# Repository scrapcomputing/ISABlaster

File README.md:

# ISA Blaster
A PCB for a software-defined ISA card powered by a Raspberry Pi Pico micro-controller.
All the logic for interfacing to the ISA bus is done in software.

# Projects based on the ISA Blaster

## DirtyRat USB Mouse Adapter
We can use the ISA Blaster as a USB mouse adapter card.
This allows you to use a USB mouse on your vintage DOS PC without the need for an external adapter.
This requires the use of:

1. The DirtyRat mouse driver for DOS: <https://github.com/scrapcomputing/DirtyRatDriver>, and
2. The DirtyRat Firmware for the Pico: <https://github.com/scrapcomputing/DirtyRatFirmware>.

# How to load the firmware
- Unplug the ISA Blaster from the motherboard
- Remove any connected USB devices (e.g., mouse)
- Press and hold the small button on the Pico
- While holding the button, connect the Pico to your PC with a micro-USB cable
- The Pico should show up as a mass-storage device
- Copy the firmware to the drive associated with the Pico
- Safely eject the mass-storage device

# Bill of materials

Gerber files are published in the releases: https://github.com/scrapcomputing/ISABlaster/releases

Item                               | # | Description
-----------------------------------|---|--------------------------------------------------------
Raspberry Pi Pico                  | 1 |
1x20-pin 2.54mm Female Headers     | 2 | For plugging in the Pico
1x20-pin 2.54mm Male Headers       | 2 | For the Pico
TXS0108EPW 20TSSOP                 | 3 | Bidirectional level-shifters 3.3V/5V
2x6 2.54mm Male Pin Headers        | 1 | For the IRQ selection
2.54mm Jumper                      | 1 | For the IRQ selection
0.1uF 1206 SMD capacitors          | 6 | Decoupling capacitors for the ICs C1-6
2.2K through-hole resistor 1/8W    | 2 | * Better to leave them unpopulated: See "Known Issues" below
3.3K through-hole resistor 1/8W    | 2 | * Better to leave them unpopulated: See "Known Issues" below
1uF through-hole ceramic capacitor | 1 | Smoothing capacitor for the board.
Horizontal Female USB connector    | 1 | For plugging in a USB device.
3-4cm short jumper wires           | 2 | For connecting Pico's TP2,TP3 pads to the PCB's pads for the on-bard USB connector

# Known Issues
- Rev0.1 connects MEMR and MEMW to voltage dividers which are made up by the 2.2K and 3.3K through-hole resistors.
  The voltage dividers can cause issues on some motherboards, so it is better to leave them unpopulated.
  This will be fixed in a later revision of the board.

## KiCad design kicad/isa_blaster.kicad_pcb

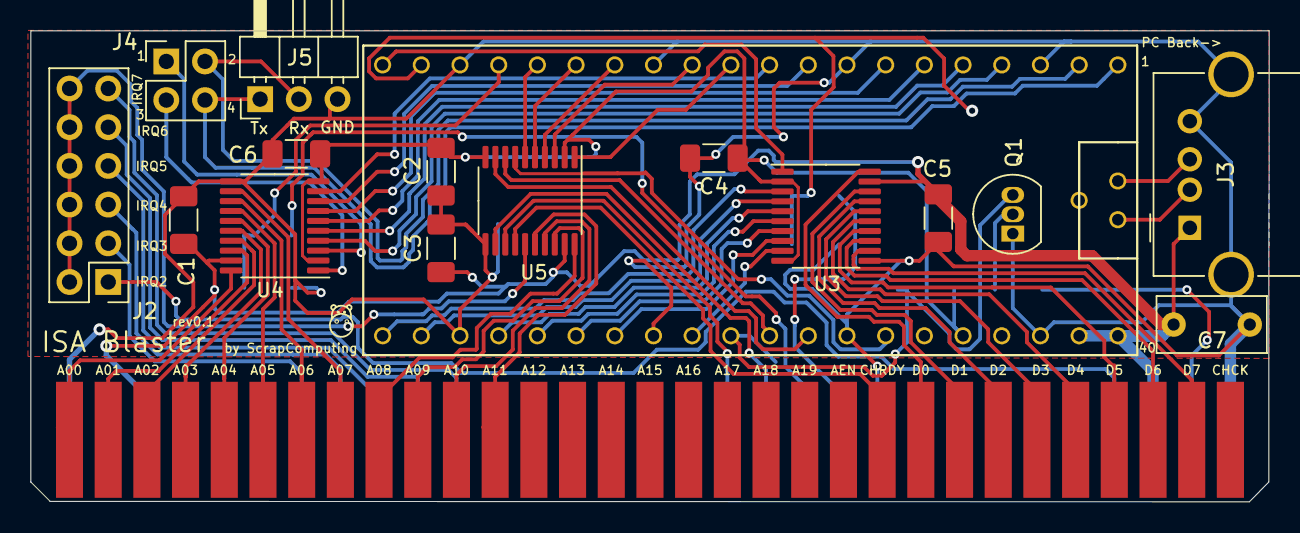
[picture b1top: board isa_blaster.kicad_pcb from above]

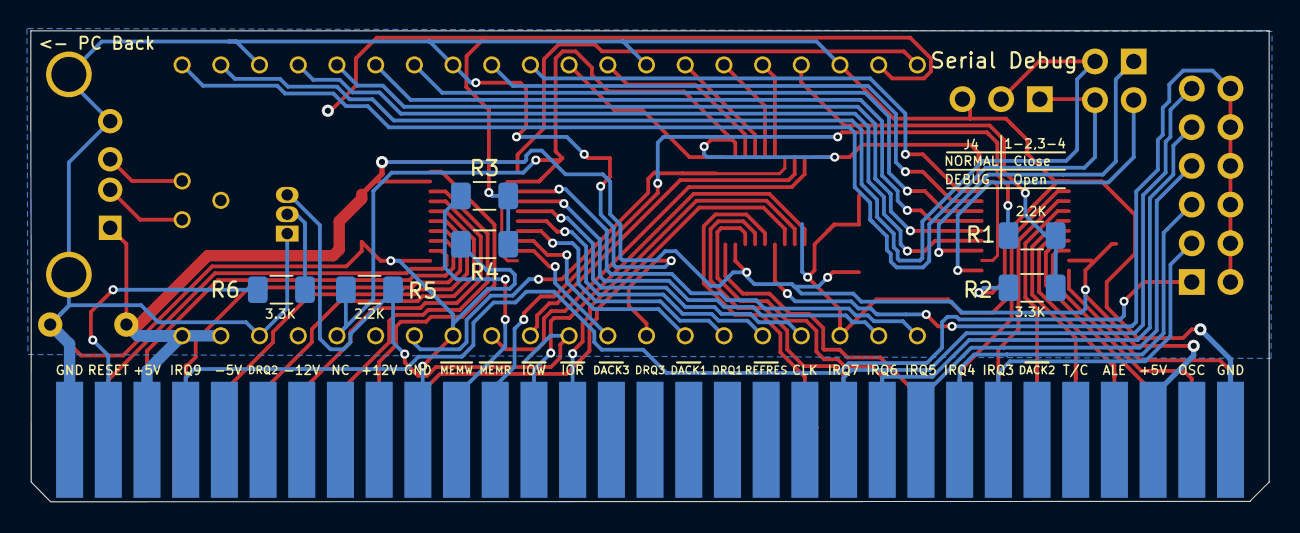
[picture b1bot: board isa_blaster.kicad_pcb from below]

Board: 2 copper layers, 81.3 x 30.9 mm, 23 parts (6 on the bottom side), 68 nets.

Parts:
C1, C2, C3, C4, C5, C6: 0.1u; C_1206_3216Metric_Pad1.33x1.80mm_HandSolder
C7: 10uF; C_Rect_L7.0mm_W3.5mm_P5.00mm
J1: Bus_ISA_8bit; 8bit_BUS_AT
J2: Conn_02x06_Odd_Even; PinHeader_2x06_P2.54mm_Vertical
J3: USB_A; USB_A_Molex_67643_Horizontal
J4: Conn_02x02_Odd_Even; PinHeader_2x02_P2.54mm_Vertical
J5: Conn_01x03; PinHeader_1x03_P2.54mm_Horizontal
Q1: 2N3904; TO-92_Inline
R1, R3, R5: 2.2K; R_1206_3216Metric_Pad1.30x1.75mm_HandSolder
R2, R4, R6: 3.3K; R_1206_3216Metric_Pad1.30x1.75mm_HandSolder
U3, U4, U5: TXS0108EPW; TSSOP-20_4.4x6.5mm_P0.65mm
U6: RaspberryPi_Pico; raspberry_pi_pico

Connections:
+3V3: C2.1, C4.1, C6.1, R5.1, U3.2, U3.10, U4.2, U4.10, U5.2, U5.10, U6.36
+5V: C1.1, C3.1, C5.1, C7.2, J1.3, J1.29, J3.1, U3.19, U4.19, U5.19, U6.39, U6.40
GND: C1.2, C2.2, C3.2, C4.2, C5.2, C6.2, C7.1, J1.1, J1.10, J1.31, J3.4, J3.5, J5.3, Q1.1, R2.2, R4.2, U3.11, U4.11, U5.11, U6.3, U6.8, U6.13, U6.18, U6.23, U6.28, U6.33, U6.38
unnamed: J1.2, R6.1
unnamed: J1.4, J2.1
unnamed: J1.11, R3.1
unnamed: J1.12, R1.1
unnamed: J1.13, U5.12
unnamed: J1.14, U5.13
unnamed: J1.21, J2.11
unnamed: J1.22, J2.9
unnamed: J1.23, J2.7
unnamed: J1.24, J2.5
unnamed: J1.25, J2.3
unnamed: J1.33, U3.12
unnamed: J1.34, U3.13
unnamed: J1.35, U3.14
unnamed: J1.36, U3.15
unnamed: J1.37, U3.16
unnamed: J1.38, U3.17
unnamed: J1.39, U3.18
unnamed: J1.40, U3.20
unnamed: J1.41, U5.14
unnamed: J1.51, U5.16
unnamed: J1.52, U5.17
unnamed: J1.53, U5.18
unnamed: J1.54, U5.20
unnamed: J1.55, U4.12
unnamed: J1.56, U4.13
unnamed: J1.57, U4.14
unnamed: J1.58, U4.15
unnamed: J1.59, U4.16
unnamed: J1.60, U4.17
unnamed: J1.61, U4.18
unnamed: J1.62, U4.20
unnamed: J2.2, J2.4, J2.6, J2.8, J2.10, J2.12, U5.15
unnamed: J3.2, U6.42
unnamed: J3.3, U6.43
unnamed: J4.1, U4.3
unnamed: J4.2, J5.2, U6.2
unnamed: J4.3, U4.1
unnamed: J4.4, J5.1, U6.1
unnamed: Q1.2, R6.2
unnamed: Q1.3, R5.2, U6.30
unnamed: R1.2, R2.1, U6.17
unnamed: R3.2, R4.1, U6.19
unnamed: U3.1, U6.20
unnamed: U3.3, U6.21
unnamed: U3.4, U6.22
unnamed: U3.5, U6.24
unnamed: U3.6, U6.25
unnamed: U3.7, U6.26
unnamed: U3.8, U6.27
unnamed: U3.9, U6.29
unnamed: U4.4, U6.4
unnamed: U4.5, U6.5
unnamed: U4.6, U6.6
unnamed: U4.7, U6.7
unnamed: U4.8, U6.9
unnamed: U4.9, U6.10
unnamed: U5.1, U6.11
unnamed: U5.3, U6.12
unnamed: U5.4, U6.14
unnamed: U5.5, U6.15
unnamed: U5.6, U6.16
unnamed: U5.7, U6.34
unnamed: U5.8, U6.31
unnamed: U5.9, U6.32

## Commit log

2023-05-15 Rev 0.1
2023-05-15 Added RESET circuit, debug header and SMD resistors
